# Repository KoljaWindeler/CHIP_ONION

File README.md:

please go to
http://koljawindeler.github.io/CHIP_ONION/

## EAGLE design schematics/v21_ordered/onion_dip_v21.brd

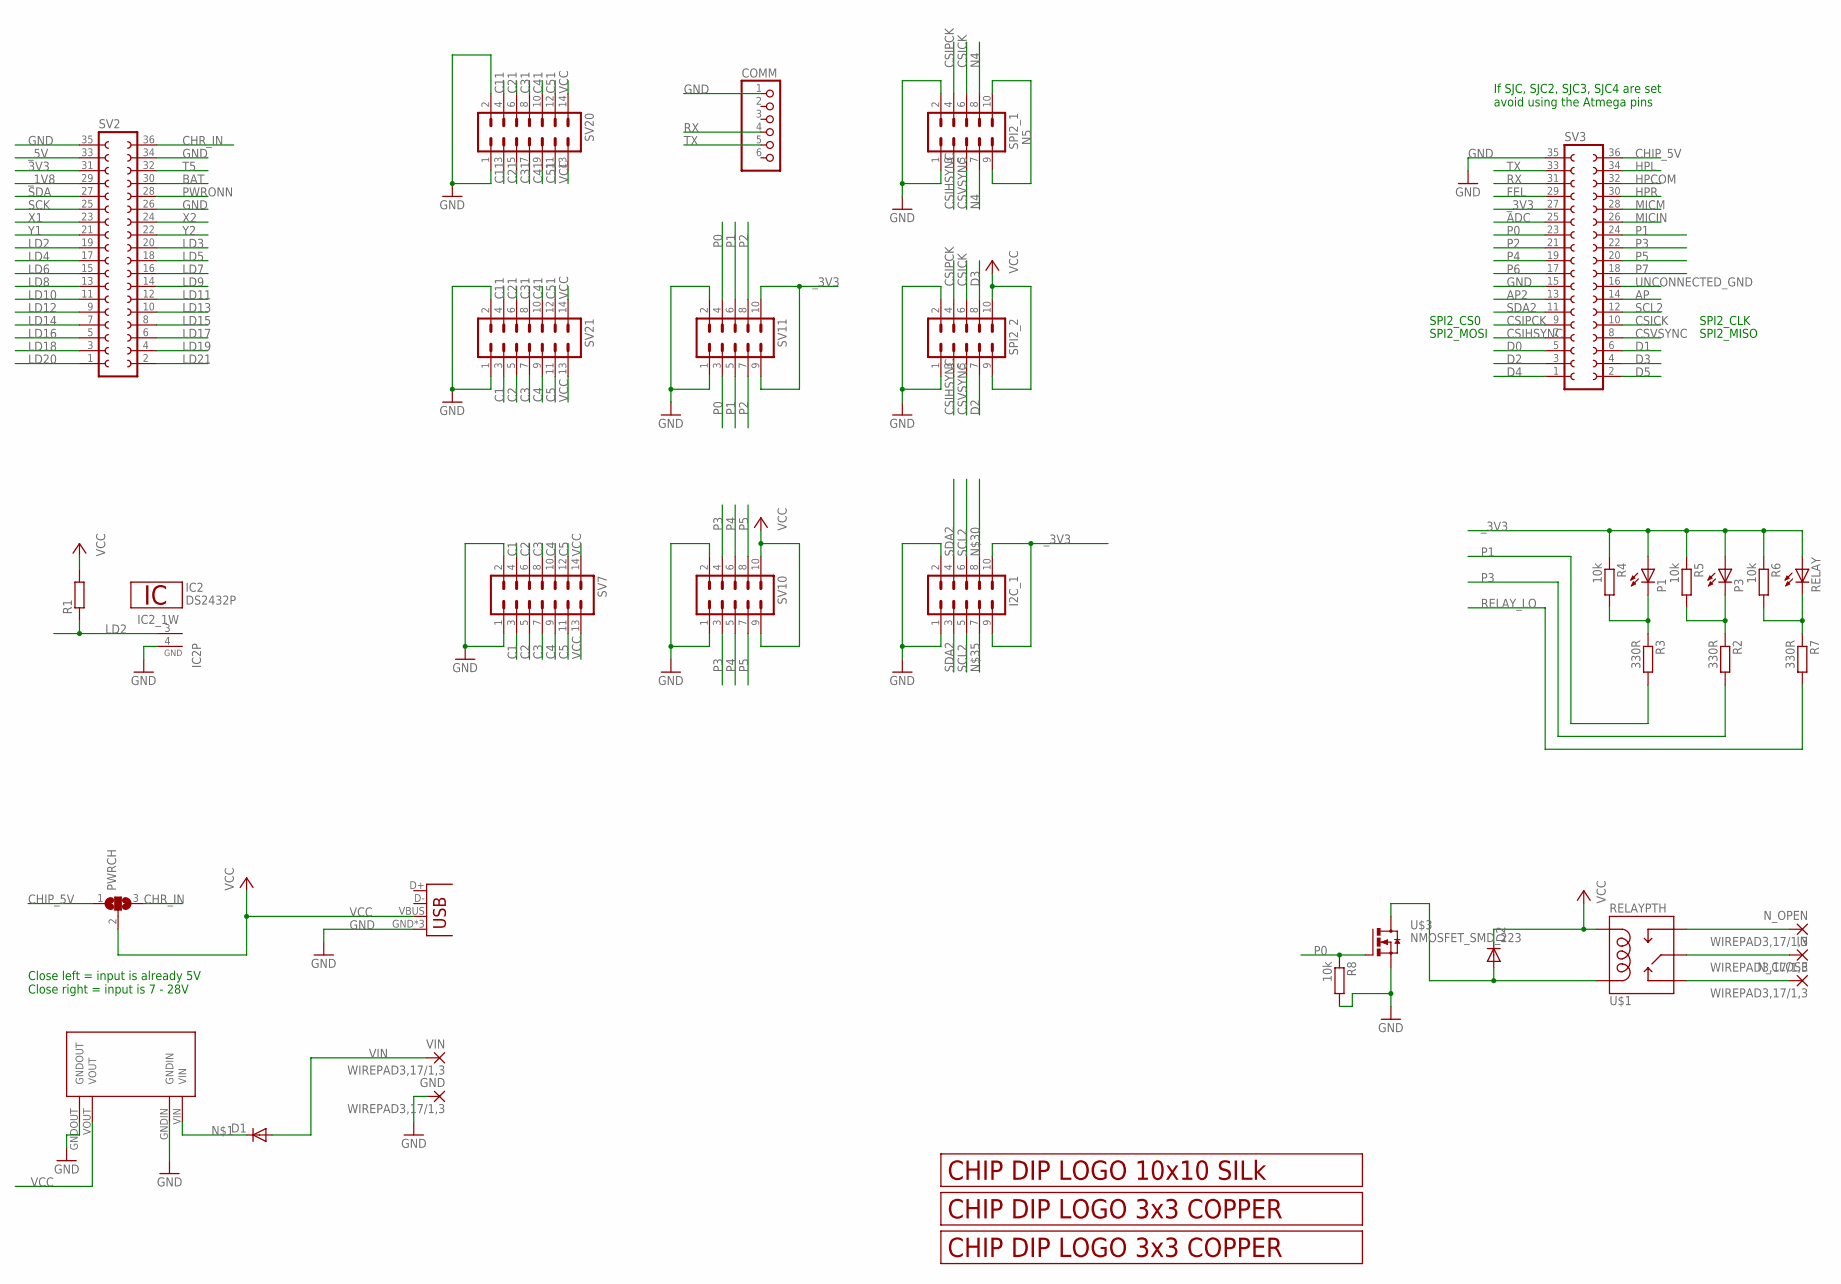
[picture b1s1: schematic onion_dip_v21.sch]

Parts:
COMM: PINHD-1X6; 1X06
D1, D2: DIODE-SMB; SMB
GND: WIREPAD3,17/1,3; 3,17/1,3
I2C_1: MA05-2
IC2: DS2432P; TSOC6
IN: WIREPAD3,17/1,3; 3,17/1,3
N_CLOSE: WIREPAD3,17/1,3; 3,17/1,3
N_OPEN: WIREPAD3,17/1,3; 3,17/1,3
P1, P3: LEDCHIP-LED0805; CHIP-LED0805
PWRCH: SJ2W; SJ_2
R1: R-EU_R0805; R0805
R2, R3, R7: 330R; R0805
R4, R5, R6, R8: 10k; R0805
RELAY: LEDCHIP-LED0805; CHIP-LED0805
SPI2_1, SPI2_2: MA05-2
SV2, SV3: FE18-2
SV7, SV20, SV21: MA07-2
SV10, SV11: MA05-2
U$1: RELAYPTH; SRD-05VDC-SL-C
U$3: NMOSFET_SMD_223; SOT223
U$4, U$6: LOGO_3X3_COPPER
U$5: LOGO_10X10_SILK
U$9: MP1584EN_FRAMELESS
USB: USBUSB-MICROB-SMT-DIP; USB-MICROB-SMT-DIP
VIN: WIREPAD3,17/1,3; 3,17/1,3

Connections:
3V3: SV2.31
ADC: SV3.25
AP: SV3.14
AP2: SV3.13
BAT: SV2.30
C1: SV7.3, SV7.4, SV21.3
C2: SV7.5, SV7.6, SV21.5
C3: SV7.7, SV7.8, SV21.7
C4: SV7.9, SV7.10, SV21.9
C5: SV7.11, SV7.12, SV21.11
C11: SV20.3, SV20.4, SV21.4
C21: SV20.5, SV20.6, SV21.6
C31: SV20.7, SV20.8, SV21.8
C41: SV20.9, SV20.10, SV21.10
C51: SV20.11, SV20.12, SV21.12
CHIP_5V: PWRCH.1, SV3.36
CHR_IN: PWRCH.3, SV2.36
CSICK: SPI2_1.6, SPI2_2.6, SV3.10
CSIHSYNC: SPI2_1.3, SPI2_2.3, SV3.7
CSIPCK: SPI2_1.4, SPI2_2.4, SV3.9
CSVSYNC: SPI2_1.5, SPI2_2.5, SV3.8
D0: SV3.5
D1: SV3.6
D2: SPI2_2.7, SV3.3
D3: SPI2_2.8, SV3.4
D4: SV3.1
D5: SV3.2
FEL: SV3.29
GND: COMM.1, GND.1, I2C_1.1, I2C_1.2, IC2.4 (GND), R8.2, SPI2_1.1, SPI2_1.2, SPI2_2.1, SPI2_2.2, SV2.26, SV2.34, SV2.35, SV3.15, SV3.35, SV7.1, SV7.2, SV10.1, SV10.2, SV11.1, SV11.2, SV20.1, SV20.2, SV21.1, SV21.2, U$3.3 (S), U$9.GNDIN, U$9.GNDOUT, USB.GND, USB.MT1 (GND), USB.MT2 (GND)
HPCOM: SV3.32
HPL: SV3.34
HPR: SV3.30
LD2: IC2.3 (1W), R1.1, SV2.19
LD3: SV2.20
LD4: SV2.17
LD5: SV2.18
LD6: SV2.15
LD7: SV2.16
LD8: SV2.13
LD9: SV2.14
LD10: SV2.11
LD11: SV2.12
LD12: SV2.9
LD13: SV2.10
LD14: SV2.7
LD15: SV2.8
LD16: SV2.5
LD17: SV2.6
LD18: SV2.3
LD19: SV2.4
LD20: SV2.1
LD21: SV2.2
MICIN: SV3.26
MICM: SV3.28
N4: SPI2_1.7, SPI2_1.8
N5: SPI2_1.9, SPI2_1.10
unnamed: D1.C, U$9.VIN
unnamed: P3.C, R2.1, R5.2
unnamed: P1.C, R3.1, R4.2
unnamed: R6.2, R7.1, RELAY.C
NCL: N_CLOSE.1, U$1.SWCLOSED (SWCLOSE)
NOP: N_OPEN.1, U$1.SWOPEN
P0: R8.1, SV3.23, SV11.3, SV11.4, U$3.1 (G)
P1: R3.2, SV3.24, SV11.5, SV11.6
P2: SV3.21, SV11.7, SV11.8
P3: R2.2, SV3.22, SV10.3, SV10.4
P4: SV3.19, SV10.5, SV10.6
P5: SV3.20, SV10.7, SV10.8
P6: SV3.17
P7: SV3.18
PWRONN: SV2.28
RELAY_LO: D2.A, R7.2, U$1.COIL1, U$3.2 (D), U$3.4 (D)
RIN: IN.1, U$1.SWCOMMON
RX: COMM.4, SV3.31
SCK: SV2.25
SCL2: I2C_1.5, I2C_1.6, SV3.12
SDA: SV2.27
SDA2: I2C_1.3, I2C_1.4, SV3.11
T5: SV2.32
TX: COMM.5, SV3.33
UNCONNECTED_GND: SV3.16
VCC: D2.C, PWRCH.2, R1.2, SPI2_2.9, SPI2_2.10, SV7.13, SV7.14, SV10.9, SV10.10, SV20.13, SV20.14, SV21.13, SV21.14, U$1.COIL0, U$9.VOUT, USB.VBUS
VIN: D1.A, VIN.1
X1: SV2.23
X2: SV2.24
Y1: SV2.21
Y2: SV2.22
_1V8: SV2.29
_3V3: I2C_1.9, I2C_1.10, P1.A, P3.A, R4.1, R5.1, R6.1, RELAY.A, SV3.27, SV11.9, SV11.10
_5V: SV2.33

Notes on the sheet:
If SJC, SJC2, SJC3, SJC4 are set avoid using the Atmega pins
Close left = input is already 5V Close right = input is 7 - 28V
SPI2_CS0
SPI2_CLK
SPI2_MOSI
SPI2_MISO

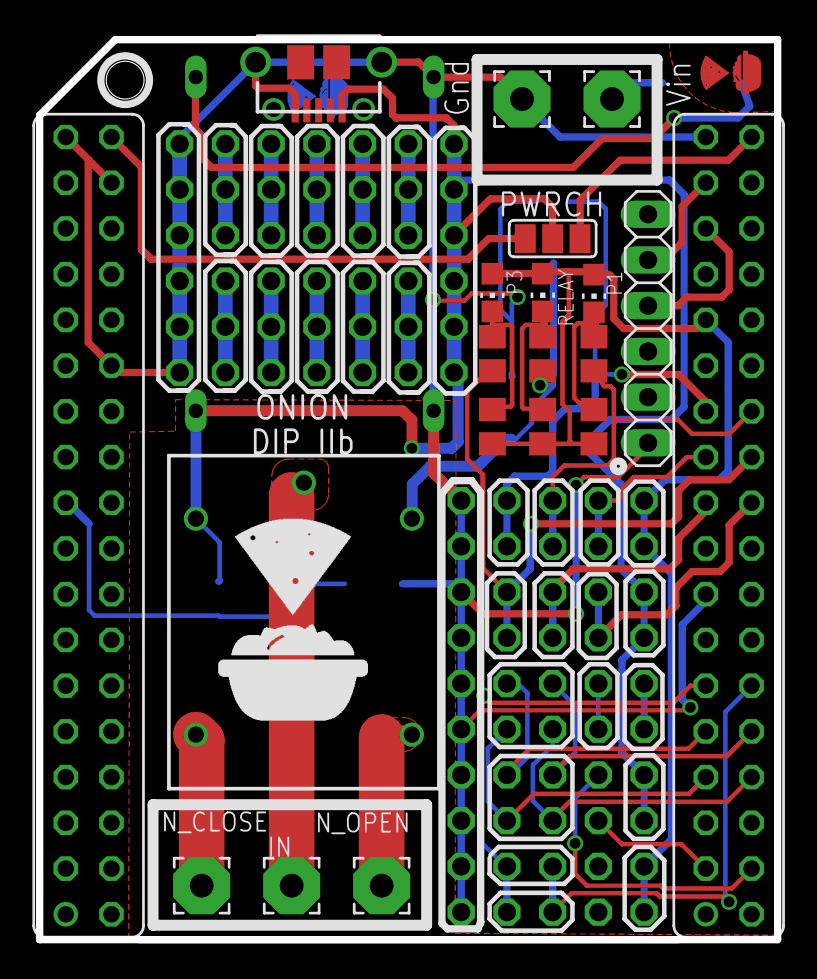
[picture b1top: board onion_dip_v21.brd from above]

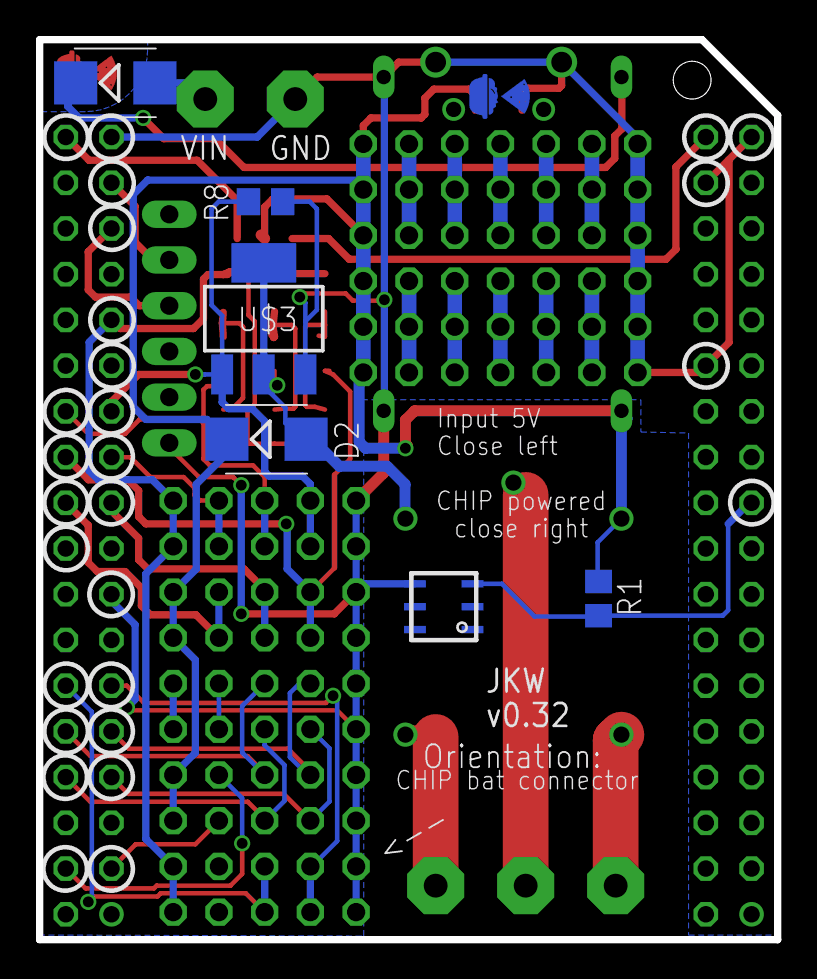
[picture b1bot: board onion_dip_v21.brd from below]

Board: 2 copper layers, 41.0 x 50.0 mm, 38 parts (7 on the bottom side), 43 nets.

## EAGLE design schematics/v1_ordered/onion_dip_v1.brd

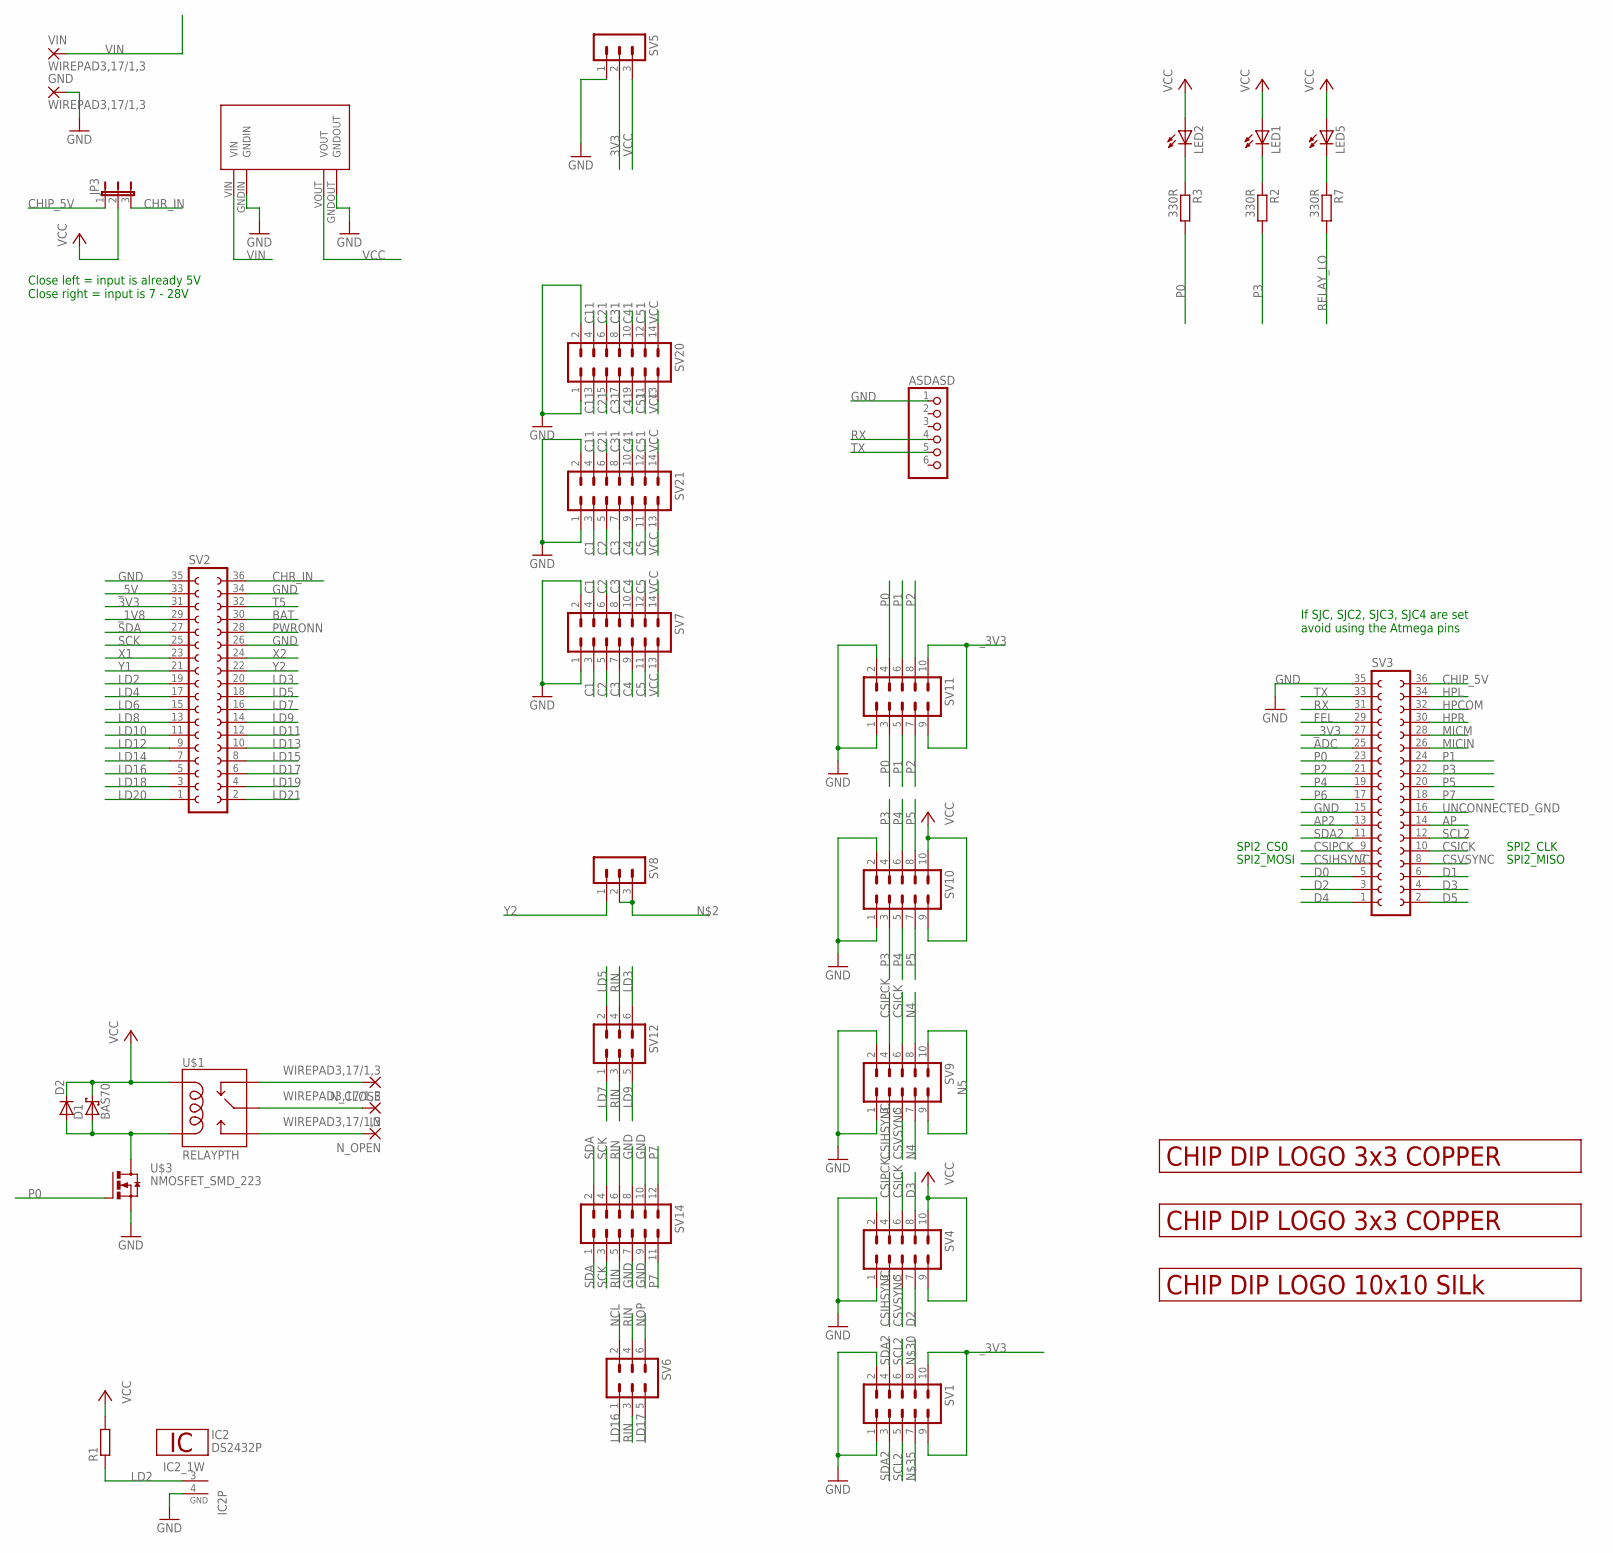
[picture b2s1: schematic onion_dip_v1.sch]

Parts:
ASDASD: PINHD-1X6; 1X06
D1: BAS70; SOT23
D2: DIODE-SMB; SMB
GND: WIREPAD3,17/1,3; 3,17/1,3
IC2: DS2432P; TSOC6
IN: WIREPAD3,17/1,3; 3,17/1,3
JP3: JP2E; JP2
LED1, LED2, LED5: LEDCHIP-LED0805; CHIP-LED0805
N_CLOSE: WIREPAD3,17/1,3; 3,17/1,3
N_OPEN: WIREPAD3,17/1,3; 3,17/1,3
R1: R-EU_R0805; R0805
R2, R3, R7: 330R; R0805
SV1, SV4, SV9, SV10, SV11: MA05-2
SV2, SV3: FE18-2
SV5, SV8: MA03-1
SV6, SV12: MA03-2
SV7, SV20, SV21: MA07-2
SV14: MA06-2
U$1: RELAYPTH; SRD-05VDC-SL-C
U$3: NMOSFET_SMD_223; SOT223
U$4, U$6: LOGO_3X3_COPPER
U$5: LOGO_10X10_SILK
U$9: MP1584EN_FRAMELESS
VIN: WIREPAD3,17/1,3; 3,17/1,3

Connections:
3V3: SV2.31, SV5.2
ADC: SV3.25
AP: SV3.14
AP2: SV3.13
BAT: SV2.30
C1: SV7.3, SV7.4, SV21.3
C2: SV7.5, SV7.6, SV21.5
C3: SV7.7, SV7.8, SV21.7
C4: SV7.9, SV7.10, SV21.9
C5: SV7.11, SV7.12, SV21.11
C11: SV20.3, SV20.4, SV21.4
C21: SV20.5, SV20.6, SV21.6
C31: SV20.7, SV20.8, SV21.8
C41: SV20.9, SV20.10, SV21.10
C51: SV20.11, SV20.12, SV21.12
CHIP_5V: JP3.1, SV3.36
CHR_IN: JP3.3, SV2.36
CSICK: SV3.10, SV4.6, SV9.6
CSIHSYNC: SV3.7, SV4.3, SV9.3
CSIPCK: SV3.9, SV4.4, SV9.4
CSVSYNC: SV3.8, SV4.5, SV9.5
D0: SV3.5
D1: SV3.6
D2: SV3.3, SV4.7
D3: SV3.4, SV4.8
D4: SV3.1
D5: SV3.2
FEL: SV3.29
GND: ASDASD.1, GND.1, IC2.4 (GND), SV1.1, SV1.2, SV2.26, SV2.34, SV2.35, SV3.15, SV3.35, SV4.1, SV4.2, SV5.1, SV7.1, SV7.2, SV9.1, SV9.2, SV10.1, SV10.2, SV11.1, SV11.2, SV14.7, SV14.8, SV14.9, SV14.10, SV20.1, SV20.2, SV21.1, SV21.2, U$3.3 (S), U$9.GNDIN, U$9.GNDOUT
HPCOM: SV3.32
HPL: SV3.34
HPR: SV3.30
LD2: IC2.3 (1W), R1.1, SV2.19
LD3: SV2.20, SV12.6
LD4: SV2.17
LD5: SV2.18, SV12.2
LD6: SV2.15
LD7: SV2.16, SV12.1
LD8: SV2.13
LD9: SV2.14, SV12.5
LD10: SV2.11
LD11: SV2.12
LD12: SV2.9
LD13: SV2.10
LD14: SV2.7
LD15: SV2.8
LD16: SV2.5, SV6.1
LD17: SV2.6, SV6.5
LD18: SV2.3
LD19: SV2.4
LD20: SV2.1
LD21: SV2.2
MICIN: SV3.26
MICM: SV3.28
N4: SV9.7, SV9.8
N5: SV9.9, SV9.10
unnamed: SV8.2, SV8.3
unnamed: LED1.C, R2.1
unnamed: LED2.C, R3.1
unnamed: LED5.C, R7.1
NCL: N_CLOSE.1, SV6.2, U$1.SWCLOSED (SWCLOSE)
NOP: N_OPEN.1, SV6.6, U$1.SWOPEN
P0: R3.2, SV3.23, SV11.3, SV11.4, U$3.1 (G)
P1: SV3.24, SV11.5, SV11.6
P2: SV3.21, SV11.7, SV11.8
P3: R2.2, SV3.22, SV10.3, SV10.4
P4: SV3.19, SV10.5, SV10.6
P5: SV3.20, SV10.7, SV10.8
P6: SV3.17
P7: SV3.18, SV14.11, SV14.12
PWRONN: SV2.28
RELAY_LO: D1.1 (A), D2.A, R7.2, U$1.COIL0, U$3.2 (D), U$3.4 (D)
RIN: IN.1, SV6.3, SV6.4, SV12.3, SV12.4, SV14.5, SV14.6, U$1.SWCOMMON
RX: ASDASD.4, SV3.31
SCK: SV2.25, SV14.3, SV14.4
SCL2: SV1.5, SV1.6, SV3.12
SDA: SV2.27, SV14.1, SV14.2
SDA2: SV1.3, SV1.4, SV3.11
T5: SV2.32
TX: ASDASD.5, SV3.33
UNCONNECTED_GND: SV3.16
VCC: D1.3 (C), D2.C, JP3.2, LED1.A, LED2.A, LED5.A, R1.2, SV4.9, SV4.10, SV5.3, SV7.13, SV7.14, SV10.9, SV10.10, SV20.13, SV20.14, SV21.13, SV21.14, U$1.COIL1, U$9.VOUT
VIN: U$9.VIN, VIN.1
X1: SV2.23
X2: SV2.24
Y1: SV2.21
Y2: SV2.22, SV8.1
_1V8: SV2.29
_3V3: SV1.9, SV1.10, SV3.27, SV11.9, SV11.10
_5V: SV2.33

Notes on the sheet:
If SJC, SJC2, SJC3, SJC4 are set avoid using the Atmega pins
Close left = input is already 5V Close right = input is 7 - 28V
SPI2_CS0
SPI2_CLK
SPI2_MOSI
SPI2_MISO

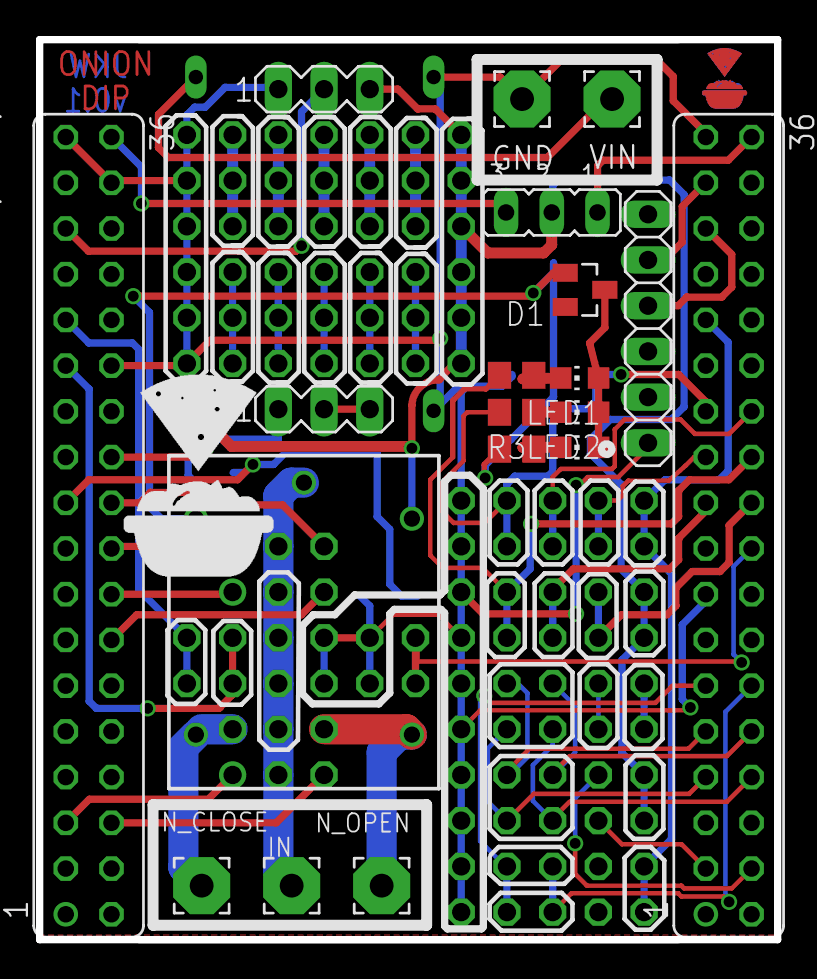
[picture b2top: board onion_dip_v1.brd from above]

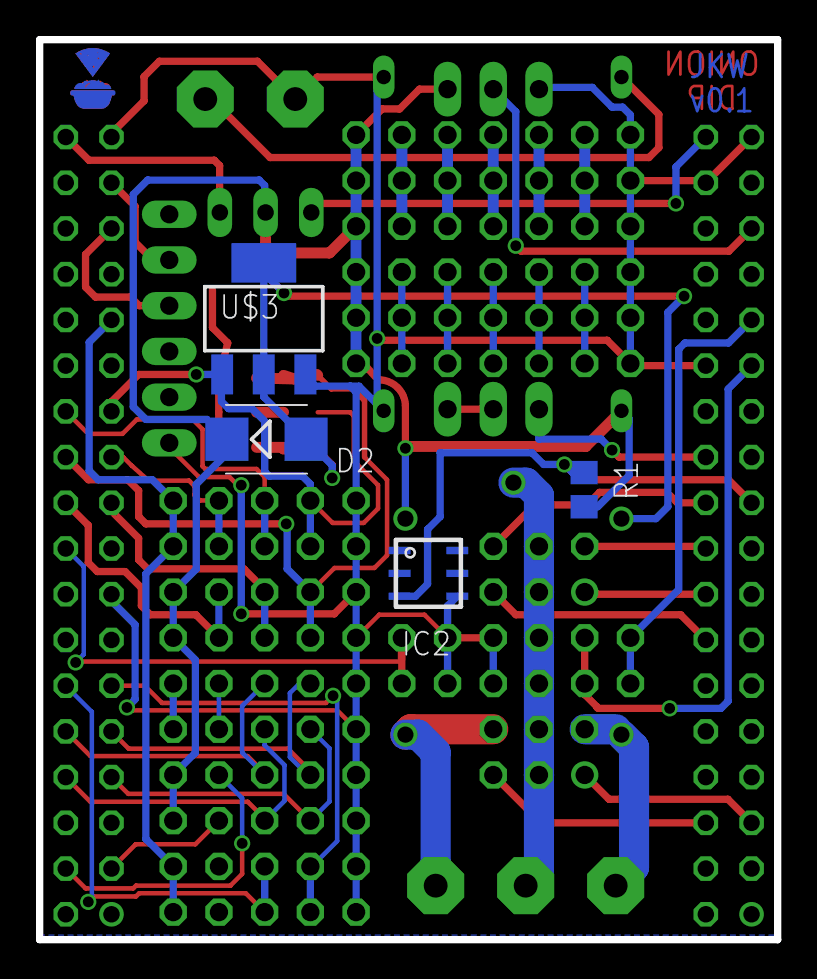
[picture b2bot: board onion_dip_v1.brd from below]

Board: 2 copper layers, 41.0 x 50.0 mm, 38 parts (5 on the bottom side), 54 nets.

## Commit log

2016-03-16 init
2016-03-16 added eeprom
2016-03-16 add screenshot v1
2016-03-16 added EEPROM, SPI, SMB Diode
2016-03-16 added UART header
2016-03-16 added relay datasheet
2016-03-16 new logo
2016-03-16 add silkscreen and forum wishes
2016-03-16 added more pins for DIP tinker area
2016-03-17 ordered
2016-03-27 add ghpages to ignore
2016-03-27 Create gh-pages branch via GitHub
2016-03-27 improved docu
2016-04-11 new version with vcc connected
2016-04-11 increased isolation
2016-04-16 v2 routing
2016-04-27 changed led to 3.3V and reconnected LED1 to P1 (was P0)
2016-04-28 added pdf schematics
2016-04-28 added sch pdf
2016-04-29 v2, clearance on relay; leds; usb jack; pulldowns
2016-04-29 removed header pin marking
2016-05-06 added version 2.1 with corner cut and silk screen improvment
2016-08-20 ordered v21
